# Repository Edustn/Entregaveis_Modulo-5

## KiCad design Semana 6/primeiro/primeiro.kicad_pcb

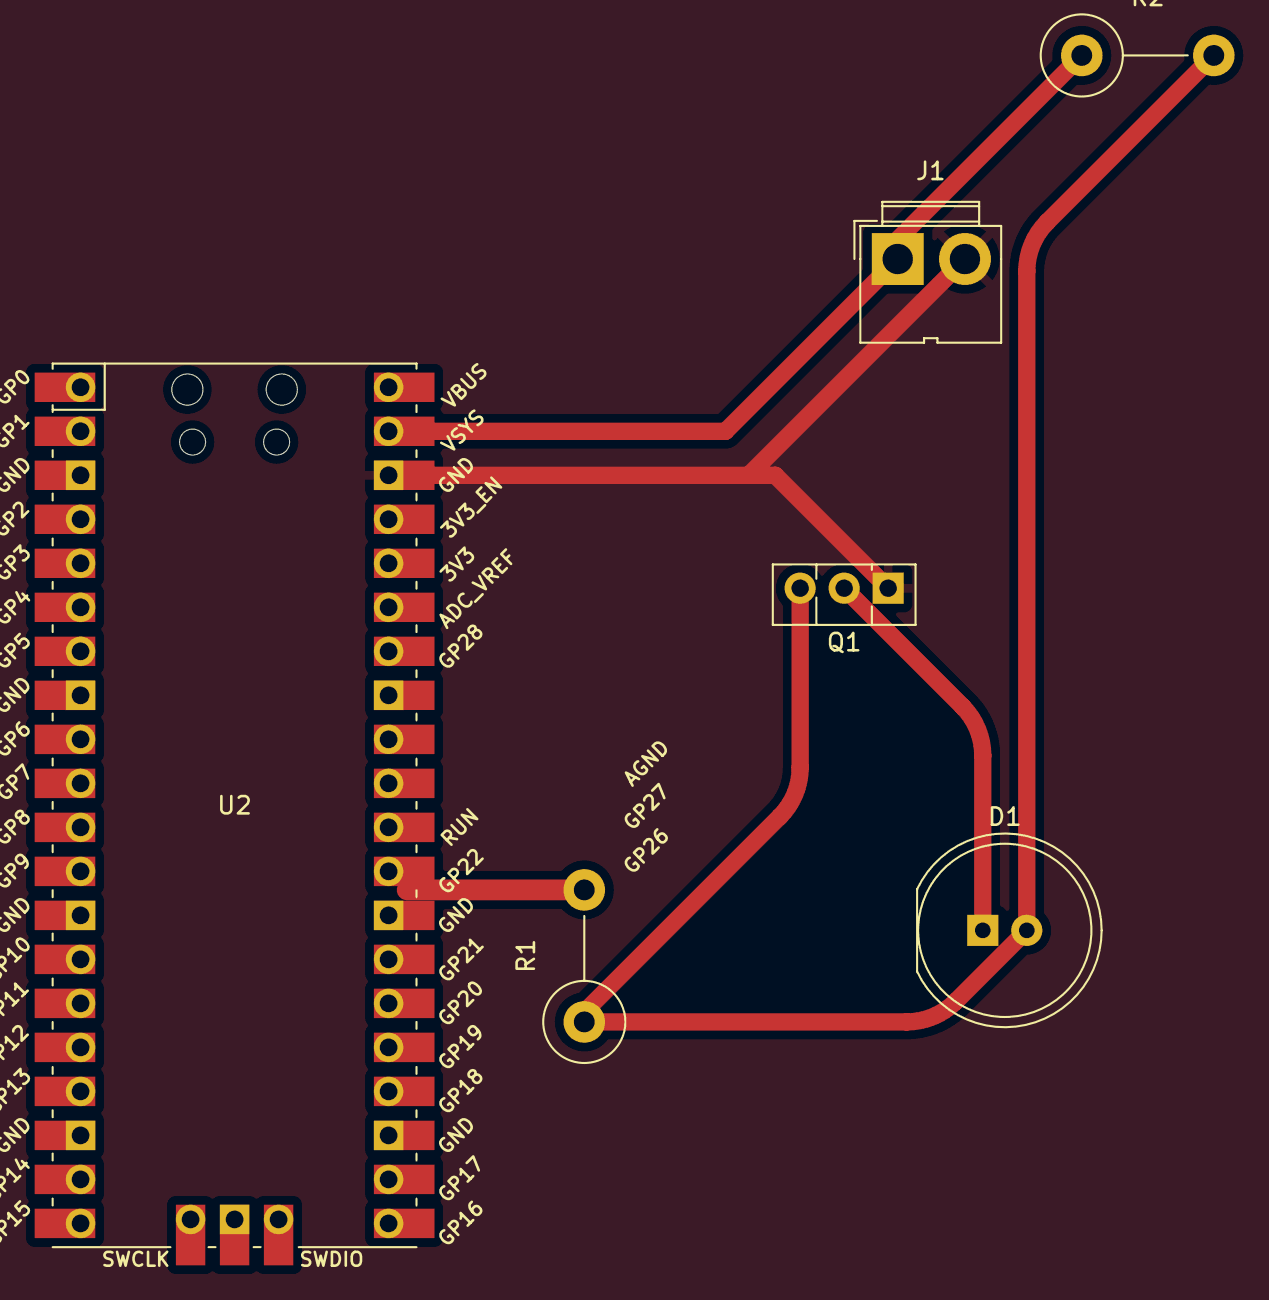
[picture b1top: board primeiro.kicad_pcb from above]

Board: 2 copper layers, 6 parts (0 on the bottom side), 5 nets.

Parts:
D1: LED; LED_D10.0mm
J1: Alimentacao; JWT_A3963_1x02_P3.96mm_Vertical
Q1: BF457 - Transistor; TO-126-3_Vertical
R1, R2: Resistor; R_Axial_DIN0414_L11.9mm_D4.5mm_P7.62mm_Vertical
U2: Pico; RPi_Pico_SMD_TH

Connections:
GND: J1.2, Q1.1 (E), U2.38 (GND)
unnamed: D1.2 (A), Q1.3 (B), R1.1, R2.2
unnamed: D1.1 (K), Q1.2 (C)
unnamed: R1.2, U2.29 (GPIO22)
VCC: J1.1, R2.1, U2.39 (VSYS)

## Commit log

2024-02-06 instalacao dos pacotes
    Foi feita a instalação dos pacotes para utilização do docusauros para pagina pessoal
2024-02-06 exclusao de arquivos que nao foram utilizados (por comentarios)
    Foi feita a exclusao dos arquivos por comentários para não aparecer na tela por enquanto, pois há uma dúvida a respeito de uma parte deve ficar. Sendo assim, tirarei a dúvida e depois será excluído p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
2024-02-06 personalizacao da minha pagina pessoal
    Foi feita minha personalizacao de pagina por meio de adicao de informacoes e imagem de perfil
2024-02-12 instalacao dos pacotes
    Foi instalado os pacotes do docusauros para comecar o projeto
2024-02-12 eliminacao de arquivos nao utilizados
    Foi eliminado os arquivos que nao serao usados no projeto
2024-02-12 Adicao de conteudo no projeto
    Foi adicionado informacos para fazer minha pagina pessoal
2024-02-13 Create static.yml
    Foi criado deploy com o Actions
2024-02-14 fix: tentando arrumar actions
2024-02-14 fix: nova tentativa
2024-02-14 fix: deploy actions
2024-02-14 fix: deploy action
2024-02-14 removendo pasta nao mais utilizada
2024-02-14 fix: consertando caminho
2024-02-14 eliminacao de item desnecessario
2024-02-14 fix: consertando baseUrl
2024-02-19 codigo
2024-02-29 feat: insere codigo para movimentacao do robo
    Foi feito um codigo para movimentacao do robo e aplicado o CLI
2024-03-01 doc: insere documentacao do funcionamento do codigo
2024-03-01 remove: remocao de codigo desnecessario
2024-03-27 insere projeto de pcb
    Foi inserido o projeto completo da PCB
2024-03-29 feat: insere dependencias e modelo de teste
2024-04-03 feat: codigo pronto
2024-04-04 doc: insere readme.md
    Foi inserido readme.md para ter o maior entendimento do codigo e como uma pessoa poderia executar esse código.
2024-04-04 fix: deleta pasta pycache e adiciona gitIgnore o venv
2024-04-04 feat: adiciona no gitIgone para nao subir pycache
2024-04-04 fix: retira venv
2024-04-04 fix: retira codigos desnecessarios
2024-04-05 fix: arruma espacamentos
